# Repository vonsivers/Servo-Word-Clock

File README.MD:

# Servo Wordclock - Version 2

Wordclock controlled by 114 servos. Improved version 2

## BoM
see "BoM.xls"

## Detailed Build Instructions
see "Assembly Instructions.pdf"

## Laser Cut
see files in folder dxf

quantity, materials and thicknesses specified in BoM

## 3D Printing
see files in folder stl

quantity and recommended materials specified in BoM

stl files named "Any" have slightly looser tolerances

## PCBs
see folder PCBs

LED_board was ordered as PCBA from PCBWay.com with black solder mask

wordclock_mainPCB was ordered as bare PCB from aisler.net

## Links
[demo video on YouTube](https://youtu.be/Euf8V2k0oOI)

[Hackaday.io project link](https://hackaday.io/project/166546-servo-controlled-word-clock-v2)

[Instructables project link](https://www.instructables.com/Servo-Wordclock-V2/)

[Version 1 Instructables project link](https://www.instructables.com/Word-Clock-Controlled-by-114-Servos/)

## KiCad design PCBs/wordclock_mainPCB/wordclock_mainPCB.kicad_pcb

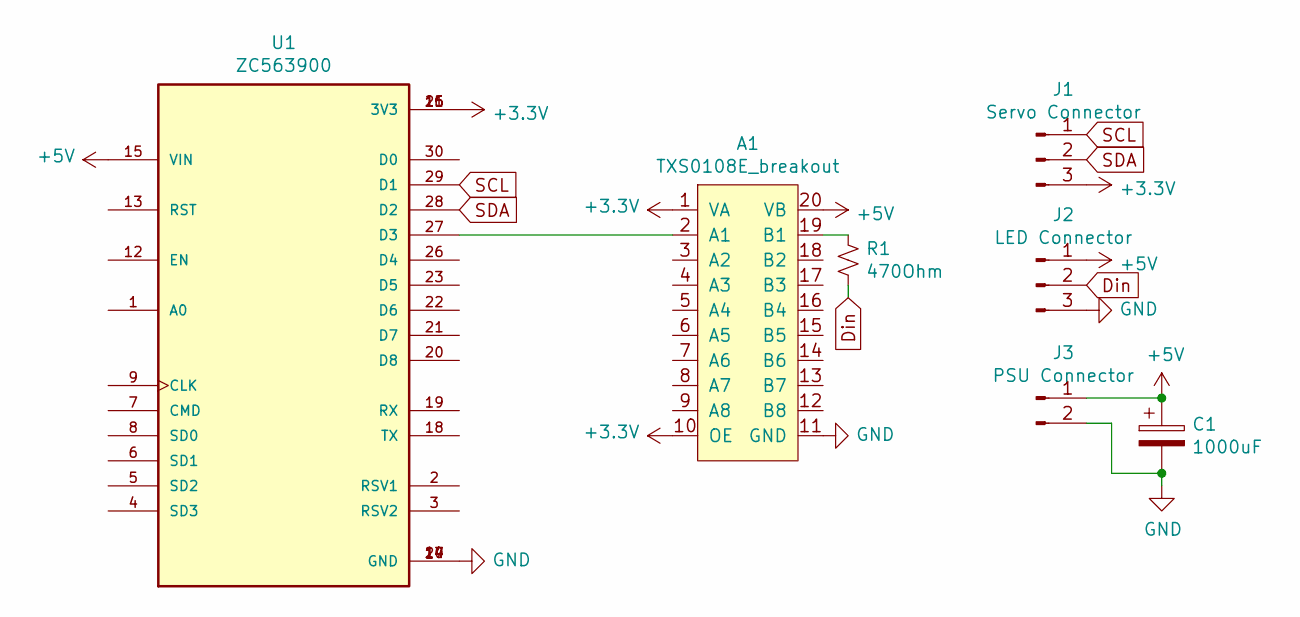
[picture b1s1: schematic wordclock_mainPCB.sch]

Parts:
A1: TXS0108E_breakout
C1: 1000uF; CP_Radial_D8.0mm_P3.50mm
J1: Servo Connector; PinSocket_1x03_P2.54mm_Vertical
J2: LED Connector; JST_XH_B3B-XH-A_1x03_P2.50mm_Vertical
J3: PSU Connector; JST_XH_B2B-XH-A_1x02_P2.50mm_Vertical
R1: 470Ohm; R_Axial_DIN0207_L6.3mm_D2.5mm_P10.16mm_Horizontal
U1: ZC563900; MODULE_ZC563900; PARTREV 1.0

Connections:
+3V3: A1.1 (VA), A1.10 (OE), J1.3, U1.11 (3V3), U1.16 (3V3), U1.25 (3V3)
+5V: A1.20 (VB), C1.1, J2.1, J3.1, U1.15 (VIN)
Din: J2.2, R1.1
GND: A1.11 (GND), C1.2, J2.3, J3.2, U1.10 (GND), U1.14 (GND), U1.17 (GND), U1.24 (GND)
unnamed: A1.2 (A1), U1.27 (D3)
unnamed: A1.19 (B1), R1.2
SCL: J1.1, U1.29 (D1)
SDA: J1.2, U1.28 (D2)

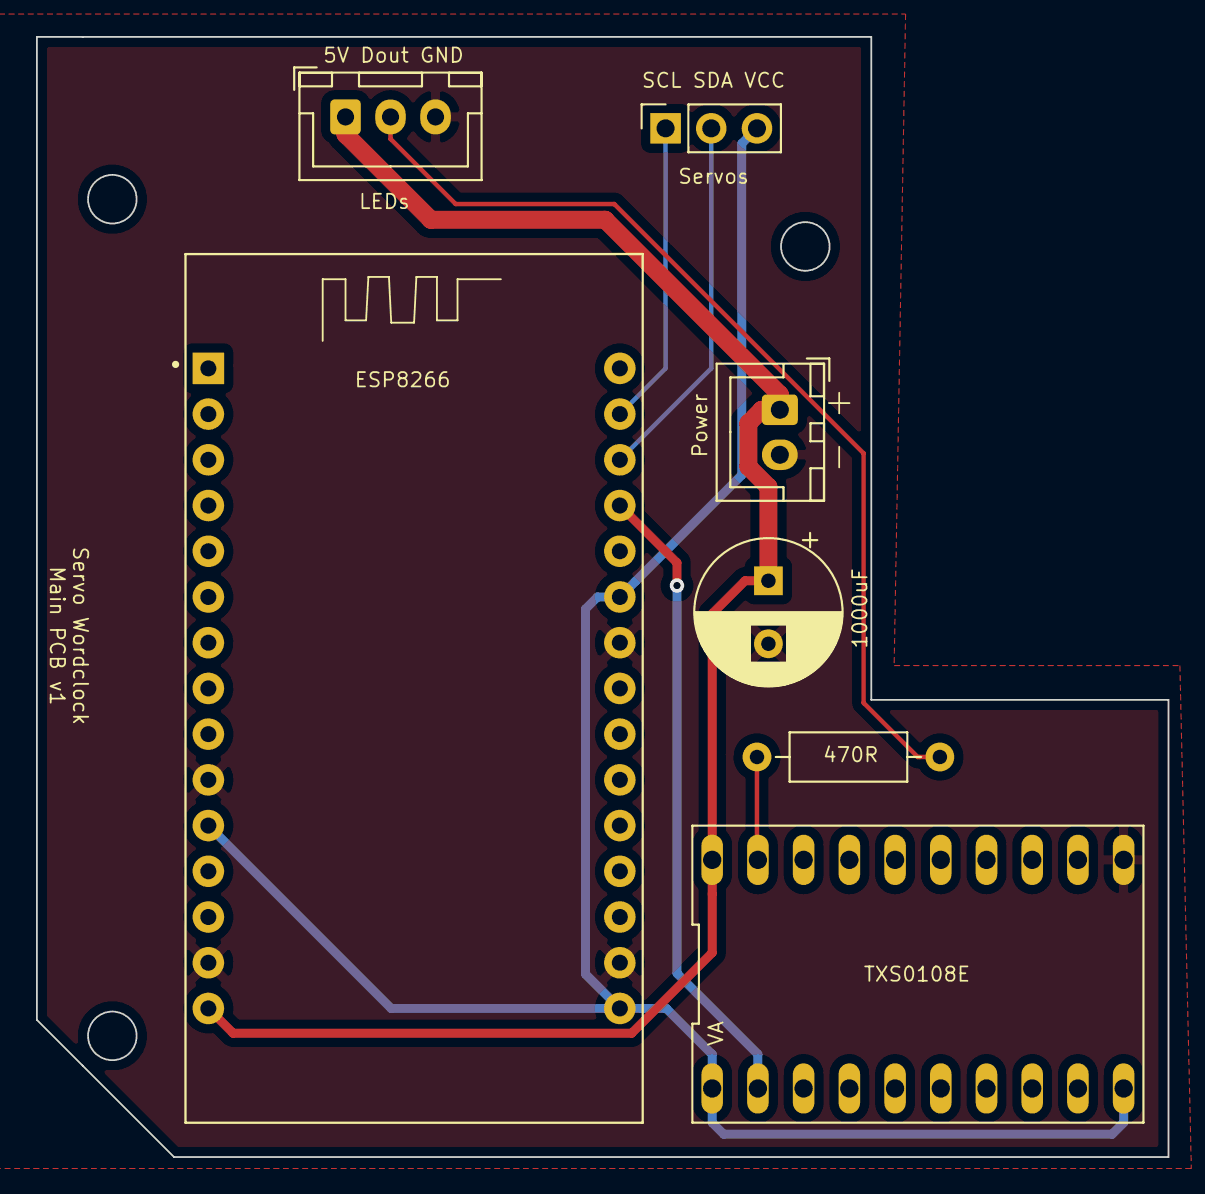
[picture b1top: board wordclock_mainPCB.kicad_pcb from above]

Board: 2 copper layers, 62.9 x 62.2 mm, 7 parts (0 on the bottom side), 8 nets.

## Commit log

2019-08-20 PCB files added
2019-09-08 added lincense file
2019-10-27 first version
2019-10-29 first really working version
2019-11-02 bug fixes
2019-11-20 Night Mode page added
    added page for night mode, added blinking clock symbol
2019-11-21 night mode added
    added night mode for swirching clock of or silent
2019-11-21 bug fixes
    night mode start time can now be larger than end time
2019-11-25 added advanced config
    added hidden advanced config options, random color bug fix, deleted other files, added lincense statement
2019-11-27 new transition between clock modes
    initialize servo position according to current clockmode; servos move slowly when changing clock mode to silent or off
2019-12-01 removed servo sleep, reassigned pins
    servo sleep mode removed, LED pin newly assigned, "no NTP" animation fixed
2020-02-27 adjusted minimum brightness to 50
2020-05-04 Added ESP8266 compatibility
    Code made compatible with ESP8266
    Fixed Exception(3) bug
    Added asynchronous WiFi search
2020-05-11 OTA + password protection
    added OTA update
    added password protection for webserver
2020-05-15 no NTP animation removed
    removed fade-in/out of clock symbol since it glitches on ESP8266
    corrected PCA9685 address
2020-11-18 added new GUI
2021-01-28 updated dependancies
2021-01-28 api update, login integriert
2021-01-28 added login and wifi settings
2021-01-29 added change password tab
2021-01-29 change pw & keep alive integriert
2021-01-29 changed path names
2021-01-29 edited Readme
2021-01-29 added move-move-build.js
2021-01-31 added build script
2021-02-01 changed ESP Filesystem, bugfixing
2021-02-01 added readme
2021-02-01 resized pics
2021-04-10 changed folder structure
2021-04-13 added MCU functions
2021-04-17 debugging
2021-04-18 debugged time change
2021-04-18 bug fixing in GUI
2021-04-19 added city names as timezones
2021-04-19 removed DST from timesettings
2021-04-19 added date to custom time
2021-04-19 changed timezone to select box
2021-08-22 mDNS fix
    fixed mDNS
    fixed minimum brightness
    set default color and effects to random
2021-10-10 added manual and buglist, updated clearFirmware.ino
2021-11-04 sleepmode for servos
2021-11-28 updated for Adafruit Servo Library 2.4.0
2021-12-12 servomax position increased to 800
2022-03-24 added stl, dxf files
    added asssembly instructions, BoM, dxf, stl files
2022-03-25 updated BoM and assembly instructions
2022-03-27 updated Assembly instructions
2022-05-02 added stl files
2022-05-04 added different gear diameters
2025-06-24 Bump pbkdf2 from 3.1.1 to 3.1.3 in /code/servowordclock-gui-develop
    Bumps [pbkdf2](https://github.com/crypto-browserify/pbkdf2) from 3.1.1 to 3.1.3.
    - [Changelog](https://github.com/browserify/pbkdf2/blob/master/CHANGELOG.md)
    - [Commits](https://github.com/crypto-browserify/pbkdf2/compare/v3.1.1...v3.1.3)
    ---
    updated-dependencies:
    - dependency-name: pbkdf2
2025-07-17 Bump on-headers and compression in /code/servowordclock-gui-develop
    Bumps [on-headers](https://github.com/jshttp/on-headers) and [compression](https://github.com/expressjs/compression). These dependencies needed to be updated together.
    Updates `on-headers` from 1.0.2 to 1.1.0
    - [Release notes](https://github.com/jshttp/on-headers/releases)
    - [Changelog](https://github.com/jshttp/on-headers/blob/master/HISTORY.md)
    - [Commits](https://github.com/jshttp/on-headers/compare/v1.0.2...v1.1.0)
    Updates `compression` from 1.7.4 to 1.8.1
2025-08-21 Bump sha.js from 2.4.11 to 2.4.12 in /code/servowordclock-gui-develop
    Bumps [sha.js](https://github.com/crypto-browserify/sha.js) from 2.4.11 to 2.4.12.
    - [Changelog](https://github.com/browserify/sha.js/blob/master/CHANGELOG.md)
    - [Commits](https://github.com/crypto-browserify/sha.js/compare/v2.4.11...v2.4.12)
    ---
    updated-dependencies:
    - dependency-name: sha.js
2025-08-21 Bump cipher-base from 1.0.4 to 1.0.6 in /code/servowordclock-gui-develop
    Bumps [cipher-base](https://github.com/crypto-browserify/cipher-base) from 1.0.4 to 1.0.6.
    - [Changelog](https://github.com/browserify/cipher-base/blob/master/CHANGELOG.md)
    - [Commits](https://github.com/crypto-browserify/cipher-base/compare/v1.0.4...v1.0.6)
    ---
    updated-dependencies:
    - dependency-name: cipher-base
2025-11-18 Bump js-yaml from 3.13.1 to 3.14.2 in /code/servowordclock-gui-develop
    Bumps [js-yaml](https://github.com/nodeca/js-yaml) from 3.13.1 to 3.14.2.
    - [Changelog](https://github.com/nodeca/js-yaml/blob/master/CHANGELOG.md)
    - [Commits](https://github.com/nodeca/js-yaml/compare/3.13.1...3.14.2)
    ---
    updated-dependencies:
    - dependency-name: js-yaml
2025-11-27 Bump node-forge and preact-cli in /code/servowordclock-gui-develop
    Bumps [node-forge](https://github.com/digitalbazaar/forge) to 1.3.2 and updates ancestor dependency [preact-cli](https://github.com/preactjs/preact-cli/tree/HEAD/packages/cli). These dependencies nee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
    Updates `node-forge` from 0.10.0 to 1.3.2
    - [Changelog](https://github.com/digitalbazaar/forge/blob/main/CHANGELOG.md)
    - [Commits](https://github.com/digitalbazaar/forge/compare/0.10.0...v1.3.2)
    Updates `preact-cli` from 3.0.5 to 3.5.1
    - [Release notes](https://github.com/preactjs/preact-cli/releases)
2026-01-24 Bump lodash from 4.17.20 to 4.17.23 in /code/servowordclock-gui-develop
    Bumps [lodash](https://github.com/lodash/lodash) from 4.17.20 to 4.17.23.
    - [Release notes](https://github.com/lodash/lodash/releases)
    - [Commits](https://github.com/lodash/lodash/compare/4.17.20...4.17.23)
    ---
    updated-dependencies:
    - dependency-name: lodash
2026-02-03 Bump url-parse from 1.4.7 to 1.5.10 in /code/servowordclock-gui-develop
    Bumps [url-parse](https://github.com/unshiftio/url-parse) from 1.4.7 to 1.5.10.
    - [Commits](https://github.com/unshiftio/url-parse/compare/1.4.7...1.5.10)
    ---
    updated-dependencies:
    - dependency-name: url-parse
    dependency-version: 1.5.10
